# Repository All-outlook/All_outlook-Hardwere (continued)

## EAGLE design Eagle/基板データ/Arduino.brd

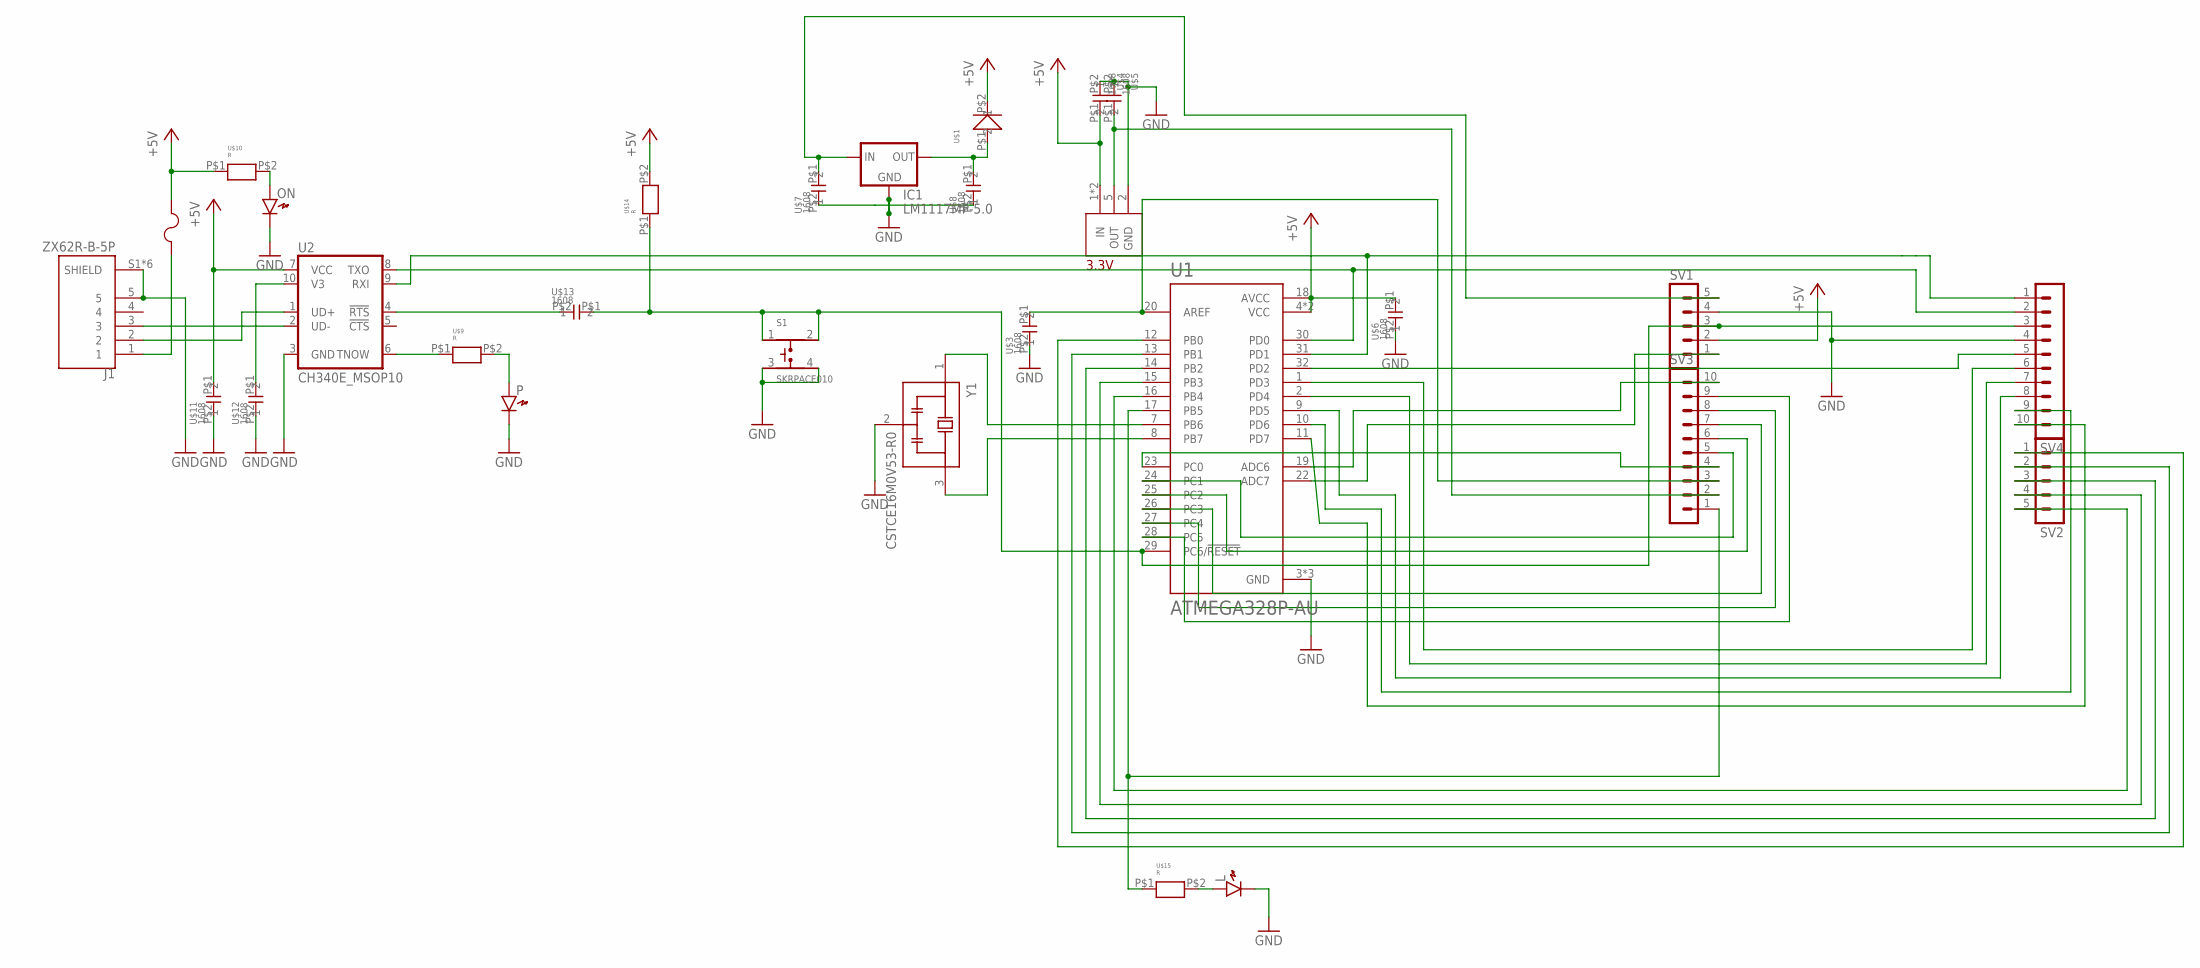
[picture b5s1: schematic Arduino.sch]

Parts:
IC1: LM1117MP-5.0; SOT223
J1: ZX62R-B-5P; HRS_ZX62R-B-5P
L: LED1608
ON: LED1608
P: LED1608
S1: SKRPACE010; SW_SKRPACE010
SV1, SV2: MA05-1
SV3, SV4: MA10-1
U1: ATMEGA328P-AU; QFP80P900X900X120-32N
U2: CH340E_MSOP10; MSOP10
U$1: D
U$2: 3.3V; SOT95P285X140-5N
U$3, U$4, U$5, U$6, U$7, U$8, U$11, U$12, U$13: 1608; CON
U$9, U$10, U$14, U$15: R; 1608
U$16: F
Y1: CSTCE16M0V53-R0; OSC_CSTCE16M0V53-R0

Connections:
+5V: SV1.2, U1.4 (VCC), U1.6 (VCC), U1.18 (AVCC), U2.7 (VCC), U$1.P$2 (2), U$2.1 (IN), U$2.3 (IN), U$4.P$1 (1), U$6.P$1 (1), U$10.P$1, U$11.P$1 (1), U$14.P$2, U$16.P$2
AREF: SV3.3, U1.20 (AREF), U$3.P$1 (1)
GND: IC1.1 (GND), J1.5, J1.S1 (SHIELD), J1.S2 (SHIELD), J1.S3 (SHIELD), J1.S4 (SHIELD), J1.S5 (SHIELD), J1.S6 (SHIELD), L.K, ON.K, P.K, S1.3, S1.4, SV1.4, SV4.4, U1.3 (GND), U1.5 (GND), U1.21 (GND), U2.3 (GND), U$2.2 (GND), U$3.P$2 (2), U$4.P$2 (2), U$5.P$2 (2), U$6.P$2 (2), U$7.P$2 (2), U$8.P$2 (2), U$11.P$2 (2), U$12.P$2 (2), Y1.2 (GND)
unnamed: U1.7 (PB6), Y1.1 (IN)
unnamed: U1.8 (PB7), Y1.3 (OUT)
unnamed: SV4.1, U1.31 (PD1), U2.9 (RXI)
unnamed: SV3.4, U1.23 (PC0)
unnamed: J1.1, U$16.P$1
unnamed: SV3.2, U$2.5 (OUT), U$5.P$1 (1)
unnamed: SV1.1, U1.22 (ADC7)
unnamed: IC1.2 (OUT), IC1.4 (OUT), U$1.P$1 (1), U$8.P$1 (1)
unnamed: IC1.3 (IN), SV1.5, U$7.P$1 (1)
unnamed: SV3.5, U1.24 (PC1)
unnamed: ON.A, U$10.P$2
unnamed: J1.2, U2.1 (UD+)
unnamed: J1.3, U2.2 (UD-)
unnamed: SV4.2, U1.30 (PD0), U2.8 (TXO)
unnamed: U2.10 (V3), U$12.P$1 (1)
unnamed: U2.6 (TNOW), U$9.P$1
unnamed: P.A, U$9.P$2
unnamed: U2.4 (!RTS), U$13.P$2 (2)
unnamed: S1.1, S1.2, SV1.3, SV4.3, U1.29 (PC6/!RESET), U$13.P$1 (1), U$14.P$1
unnamed: SV3.10, U1.19 (ADC6)
unnamed: SV3.6, U1.25 (PC2)
unnamed: SV3.7, U1.26 (PC3)
unnamed: SV3.8, U1.27 (PC4)
unnamed: SV3.9, U1.28 (PC5)
unnamed: SV3.1, U1.17 (PB5), U$15.P$1
unnamed: SV2.5, U1.16 (PB4)
unnamed: SV2.4, U1.15 (PB3)
unnamed: SV2.3, U1.14 (PB2)
unnamed: SV2.2, U1.13 (PB1)
unnamed: SV2.1, U1.12 (PB0)
unnamed: SV4.8, U1.9 (PD5)
unnamed: SV4.5, U1.32 (PD2)
unnamed: SV4.6, U1.1 (PD3)
unnamed: SV4.7, U1.2 (PD4)
unnamed: SV4.9, U1.10 (PD6)
unnamed: SV4.10, U1.11 (PD7)
unnamed: L.A, U$15.P$2

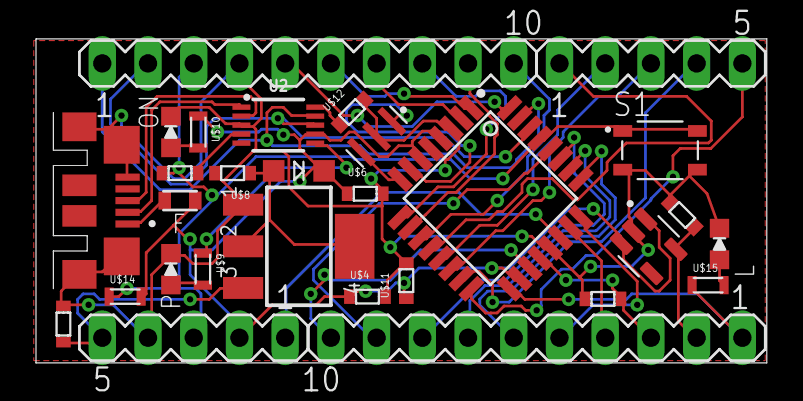
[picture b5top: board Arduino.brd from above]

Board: 2 copper layers, 40.6 x 18.0 mm, 29 parts (0 on the bottom side), 40 nets.

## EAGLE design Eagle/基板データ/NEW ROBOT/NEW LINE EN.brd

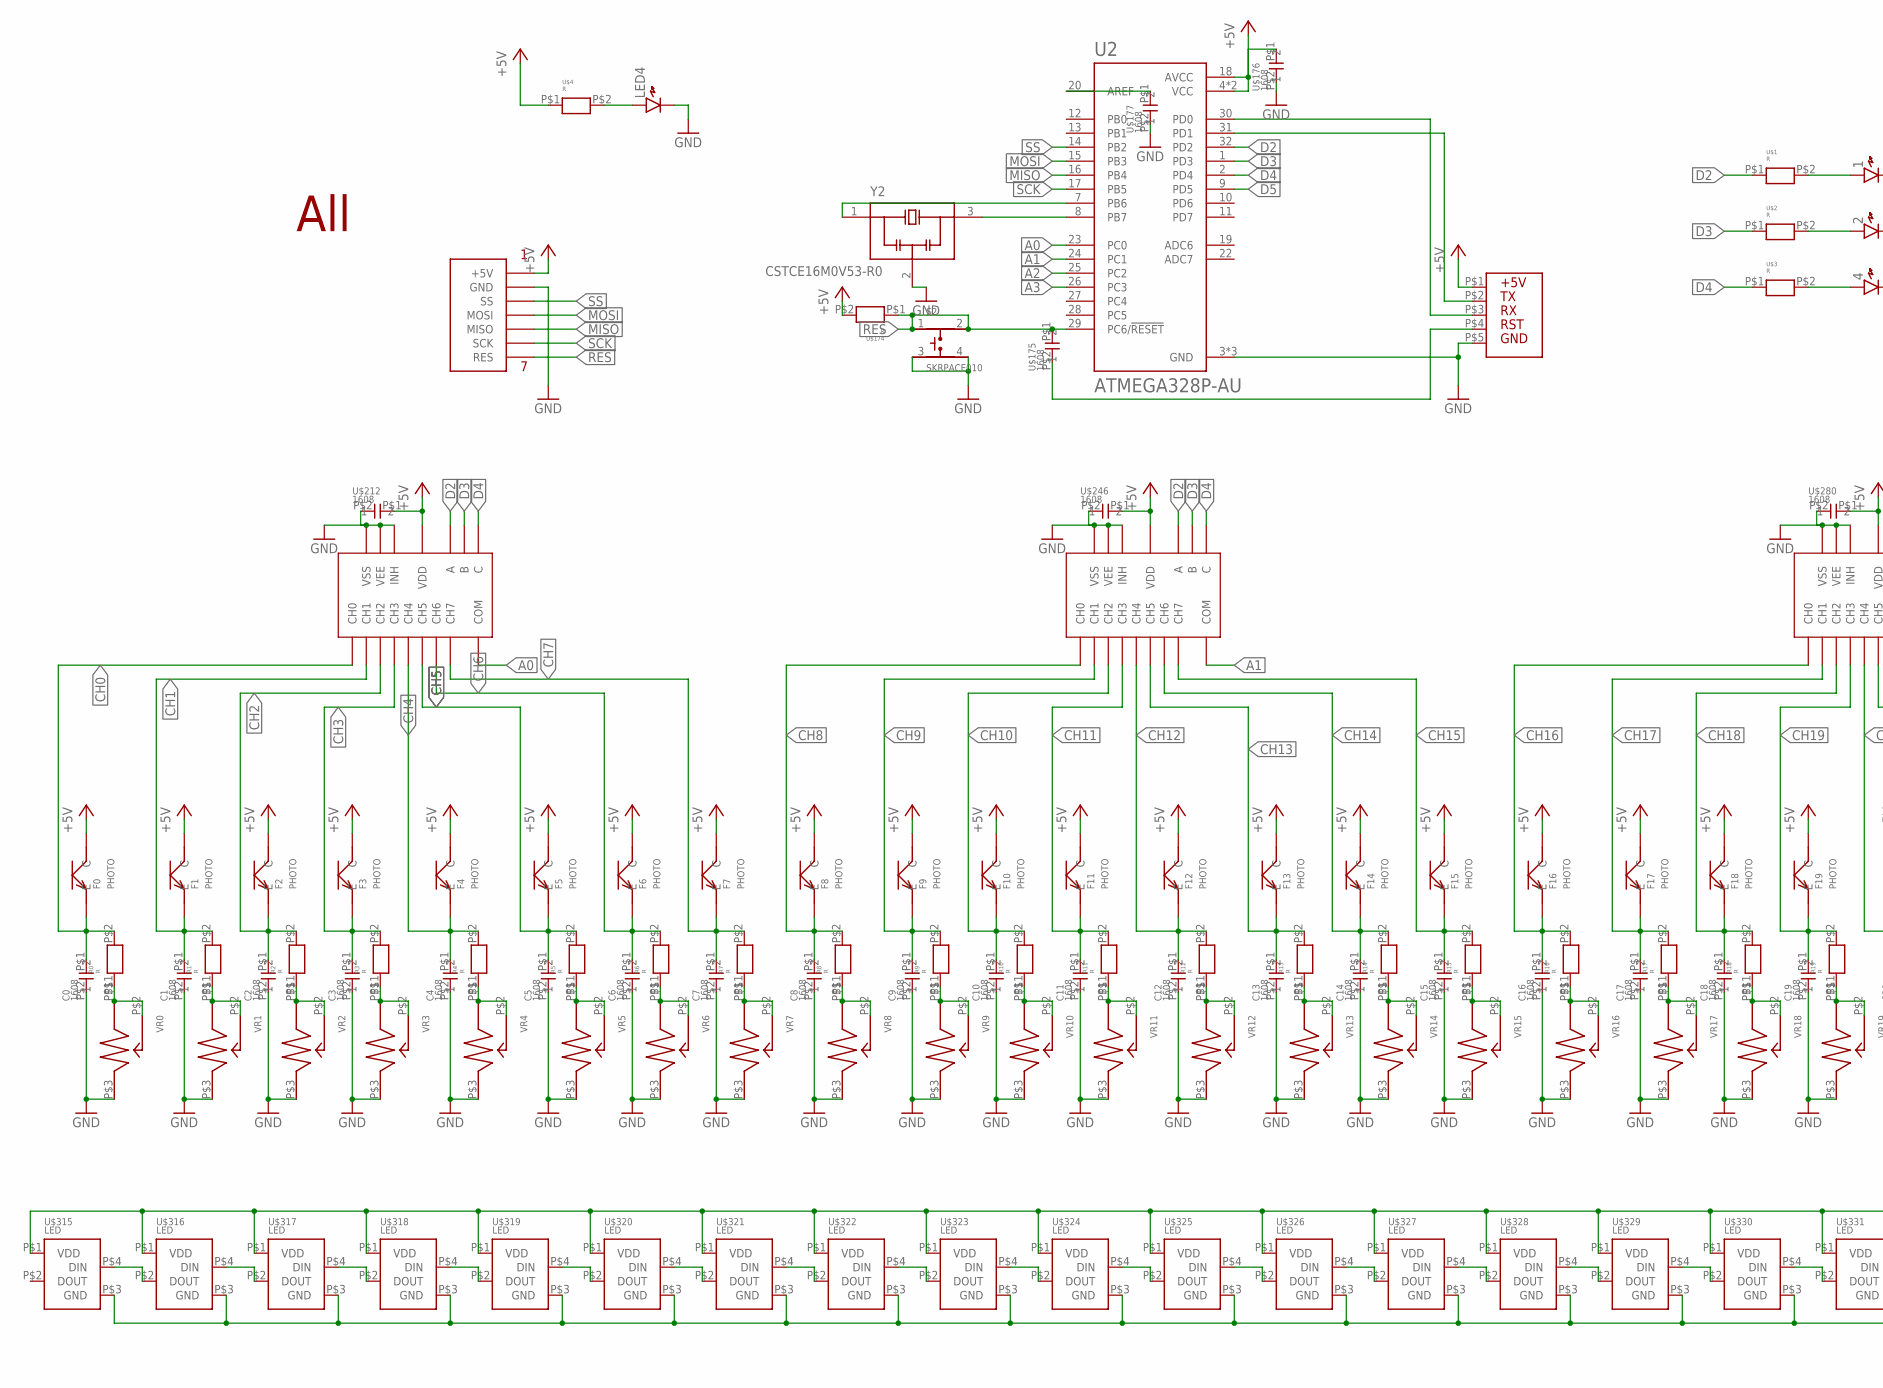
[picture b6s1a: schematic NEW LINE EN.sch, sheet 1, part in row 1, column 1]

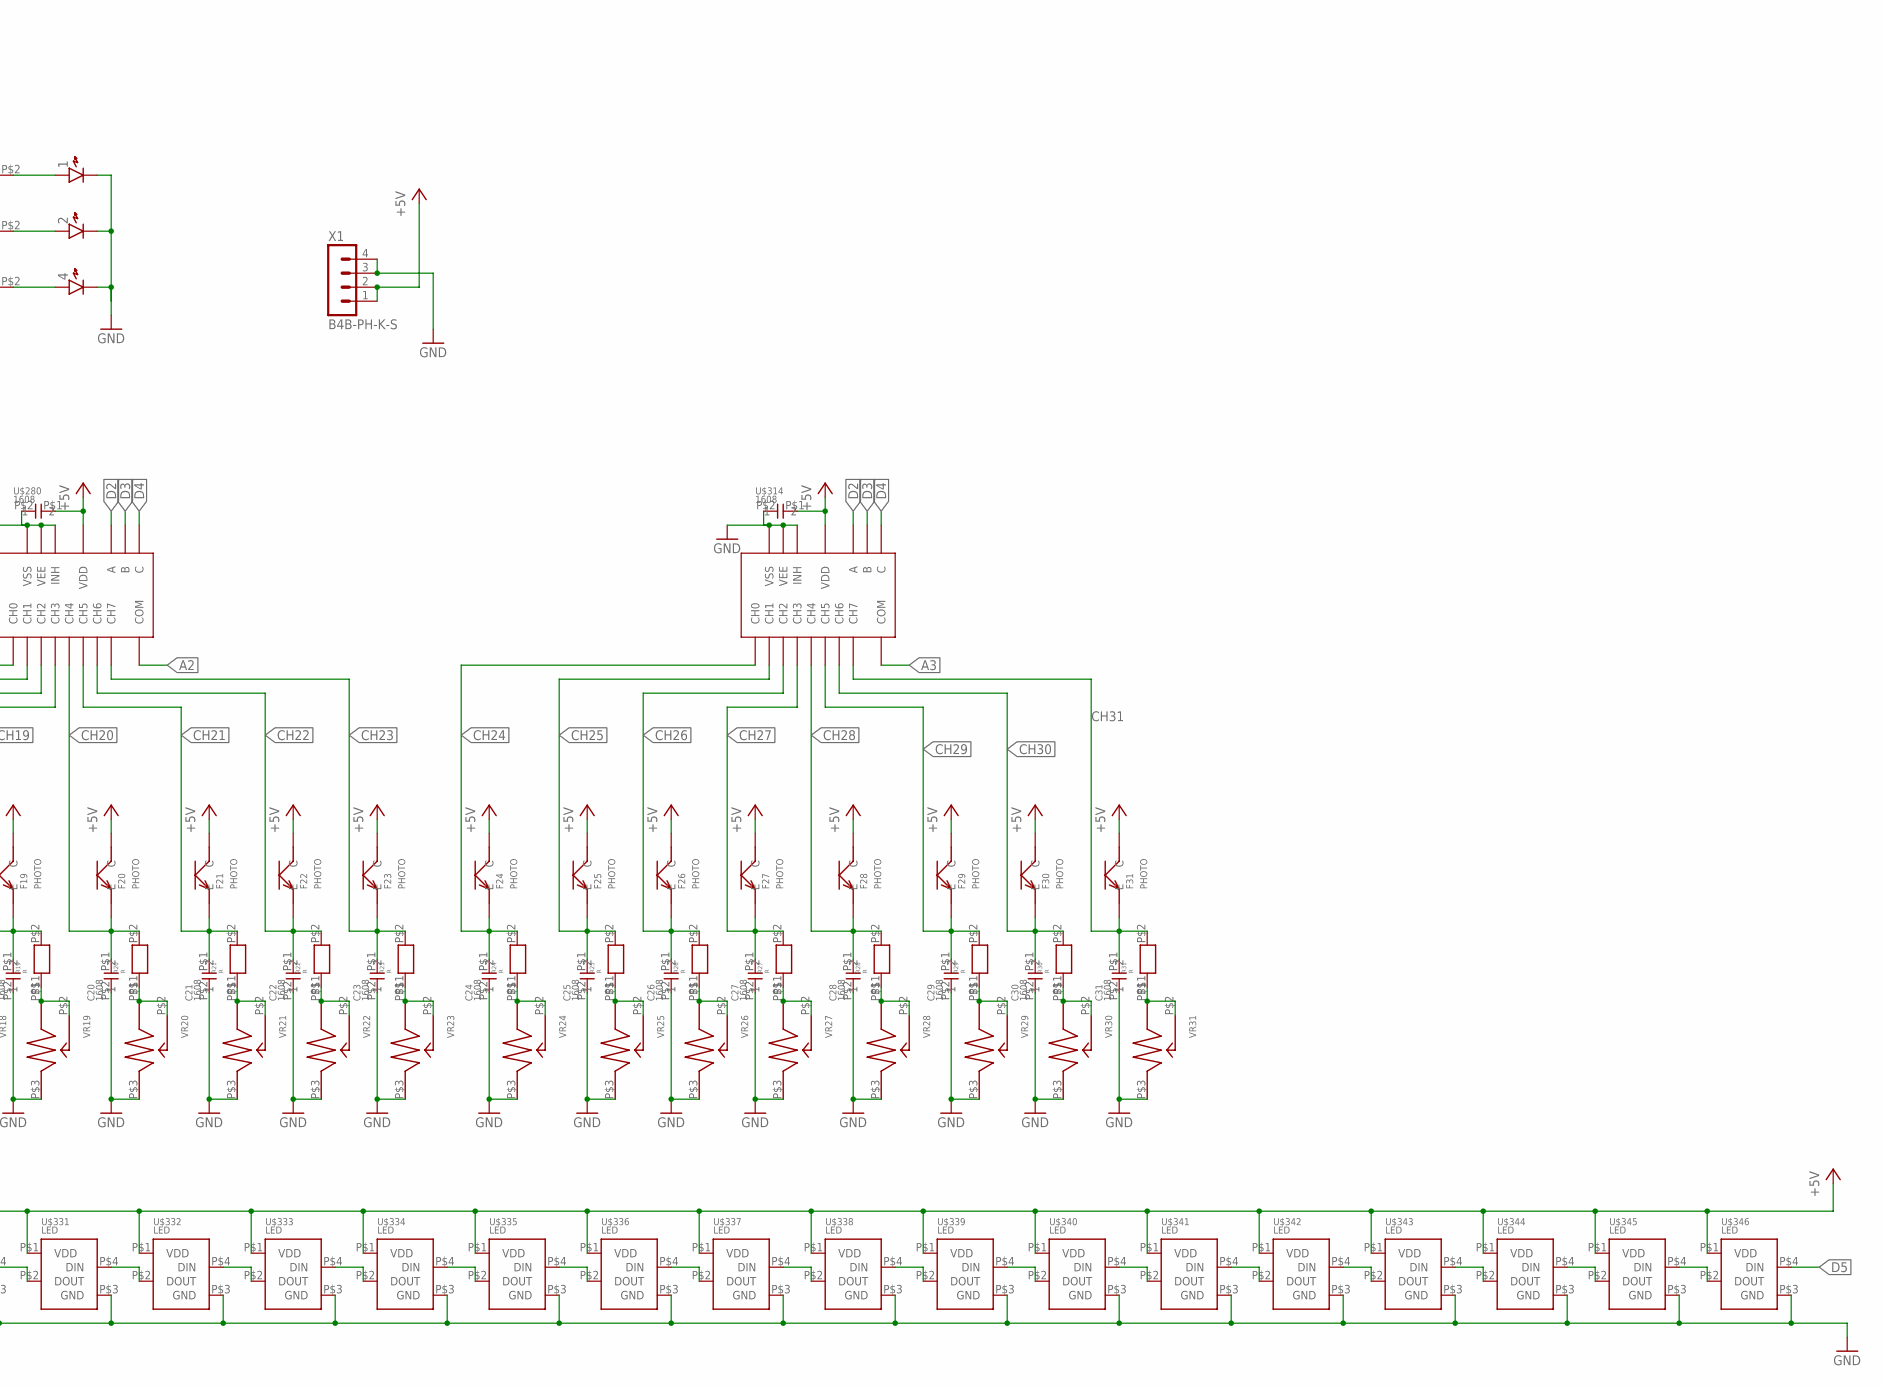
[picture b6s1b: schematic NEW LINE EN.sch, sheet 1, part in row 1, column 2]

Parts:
1, 2, 4: LED1608
C0, C1, C2, C3, C4, C5, C6, C7, C8, C9, C10, C11, C12, C13, C14, C15, C16, C17, C18, C19, C20, C21, C22, C23, C24, C25, C26, C27, C28, C29, C30, C31: 1608; CON
F0, F1, F2, F3, F4, F5, F6, F7, F8, F9, F10, F11, F12, F13, F14, F15, F16, F17, F18, F19, F20, F21, F22, F23, F24, F25, F26, F27, F28, F29, F30, F31: PHOTO
LED4: LED1608
R0, R1, R2, R3, R4, R5, R6, R7, R8, R9, R10, R11, R12, R13, R14, R15, R16, R17, R18, R19, R20, R21, R22, R23, R24, R25, R26, R27, R28, R29, R30, R31: R; 1608
S2: SKRPACE010; SW_SKRPACE010
U2: ATMEGA328P-AU; QFP80P900X900X120-32N
U$1, U$2, U$3, U$4, U$174: R; 1608
U$5: SPI
U$6: SI
U$7: ALL
U$175, U$176, U$177, U$212, U$246, U$280, U$314: 1608; CON
U$179, U$213, U$247, U$281: AM; SOP65P640X120-16N
U$315, U$316, U$317, U$318, U$319, U$320, U$321, U$322, U$323, U$324, U$325, U$326, U$327, U$328, U$329, U$330, U$331, U$332, U$333, U$334, U$335, U$336, U$337, U$338, U$339, U$340, U$341, U$342, U$343, U$344, U$345, U$346: LED
VR0, VR1, VR2, VR3, VR4, VR5, VR6, VR7, VR8, VR9, VR10, VR11, VR12, VR13, VR14, VR15, VR16, VR17, VR18, VR19, VR20, VR21, VR22, VR23, VR24, VR25, VR26, VR27, VR28, VR29, VR30, VR31: VR
X1: B4B-PH-K-S
Y2: CSTCE16M0V53-R0; OSC_CSTCE16M0V53-R0

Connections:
+5V: F0.P$1 (C), F1.P$1 (C), F2.P$1 (C), F3.P$1 (C), F4.P$1 (C), F5.P$1 (C), F6.P$1 (C), F7.P$1 (C), F8.P$1 (C), F9.P$1 (C), F10.P$1 (C), F11.P$1 (C), F12.P$1 (C), F13.P$1 (C), F14.P$1 (C), F15.P$1 (C), F16.P$1 (C), F17.P$1 (C), F18.P$1 (C), F19.P$1 (C), F20.P$1 (C), F21.P$1 (C), F22.P$1 (C), F23.P$1 (C), F24.P$1 (C), F25.P$1 (C), F26.P$1 (C), F27.P$1 (C), F28.P$1 (C), F29.P$1 (C), F30.P$1 (C), F31.P$1 (C), U2.4 (VCC), U2.6 (VCC), U2.18 (AVCC), U$4.P$1, U$5.P$1 (+5V), U$6.P$1, U$174.P$2, U$176.P$1 (1), U$179.16 (VDD), U$212.P$1 (1), U$213.16 (VDD), U$246.P$1 (1), U$247.16 (VDD), U$280.P$1 (1), U$281.16 (VDD), U$314.P$1 (1), U$315.P$1 (VDD), U$316.P$1 (VDD), U$317.P$1 (VDD), U$318.P$1 (VDD), U$319.P$1 (VDD), U$320.P$1 (VDD), U$321.P$1 (VDD), U$322.P$1 (VDD), U$323.P$1 (VDD), U$324.P$1 (VDD), U$325.P$1 (VDD), U$326.P$1 (VDD), U$327.P$1 (VDD), U$328.P$1 (VDD), U$329.P$1 (VDD), U$330.P$1 (VDD), U$331.P$1 (VDD), U$332.P$1 (VDD), U$333.P$1 (VDD), U$334.P$1 (VDD), U$335.P$1 (VDD), U$336.P$1 (VDD), U$337.P$1 (VDD), U$338.P$1 (VDD), U$339.P$1 (VDD), U$340.P$1 (VDD), U$341.P$1 (VDD), U$342.P$1 (VDD), U$343.P$1 (VDD), U$344.P$1 (VDD), U$345.P$1 (VDD), U$346.P$1 (VDD), X1.1, X1.2
A0: U2.23 (PC0), U$179.3 (COM)
A1: U2.24 (PC1), U$213.3 (COM)
A2: U2.25 (PC2), U$247.3 (COM)
A3: U2.26 (PC3), U$281.3 (COM)
CH0: C0.P$1 (1), F0.P$2 (E), R0.P$2, U$179.13 (CH0)
CH1: C1.P$1 (1), F1.P$2 (E), R1.P$2, U$179.14 (CH1)
CH2: C2.P$1 (1), F2.P$2 (E), R2.P$2, U$179.15 (CH2)
CH3: C3.P$1 (1), F3.P$2 (E), R3.P$2, U$179.12 (CH3)
CH4: C4.P$1 (1), F4.P$2 (E), R4.P$2, U$179.1 (CH4)
CH5: C5.P$1 (1), F5.P$2 (E), R5.P$2, U$179.5 (CH5)
CH6: C6.P$1 (1), F6.P$2 (E), R6.P$2, U$179.2 (CH6)
CH7: C7.P$1 (1), F7.P$2 (E), R7.P$2, U$179.4 (CH7)
CH8: C8.P$1 (1), F8.P$2 (E), R8.P$2, U$213.13 (CH0)
CH9: C9.P$1 (1), F9.P$2 (E), R9.P$2, U$213.14 (CH1)
CH10: C10.P$1 (1), F10.P$2 (E), R10.P$2, U$213.15 (CH2)
CH11: C11.P$1 (1), F11.P$2 (E), R11.P$2, U$213.12 (CH3)
CH12: C12.P$1 (1), F12.P$2 (E), R12.P$2, U$213.1 (CH4)
CH13: C13.P$1 (1), F13.P$2 (E), R13.P$2, U$213.5 (CH5)
CH14: C14.P$1 (1), F14.P$2 (E), R14.P$2, U$213.2 (CH6)
CH15: C15.P$1 (1), F15.P$2 (E), R15.P$2, U$213.4 (CH7)
CH16: C16.P$1 (1), F16.P$2 (E), R16.P$2, U$247.13 (CH0)
CH17: C17.P$1 (1), F17.P$2 (E), R17.P$2, U$247.14 (CH1)
CH18: C18.P$1 (1), F18.P$2 (E), R18.P$2, U$247.15 (CH2)
CH19: C19.P$1 (1), F19.P$2 (E), R19.P$2, U$247.12 (CH3)
CH20: C20.P$1 (1), F20.P$2 (E), R20.P$2, U$247.1 (CH4)
CH21: C21.P$1 (1), F21.P$2 (E), R21.P$2, U$247.5 (CH5)
CH22: C22.P$1 (1), F22.P$2 (E), R22.P$2, U$247.2 (CH6)
CH23: C23.P$1 (1), F23.P$2 (E), R23.P$2, U$247.4 (CH7)
CH24: C24.P$1 (1), F24.P$2 (E), R24.P$2, U$281.13 (CH0)
CH25: C25.P$1 (1), F25.P$2 (E), R25.P$2, U$281.14 (CH1)
CH26: C26.P$1 (1), F26.P$2 (E), R26.P$2, U$281.15 (CH2)
CH27: C27.P$1 (1), F27.P$2 (E), R27.P$2, U$281.12 (CH3)
CH28: C28.P$1 (1), F28.P$2 (E), R28.P$2, U$281.1 (CH4)
CH29: C29.P$1 (1), F29.P$2 (E), R29.P$2, U$281.5 (CH5)
CH30: C30.P$1 (1), F30.P$2 (E), R30.P$2, U$281.2 (CH6)
CH31: C31.P$1 (1), F31.P$2 (E), R31.P$2, U$281.4 (CH7)
D2: U2.32 (PD2), U$1.P$1, U$179.11 (A), U$213.11 (A), U$247.11 (A), U$281.11 (A)
D3: U2.1 (PD3), U$2.P$1, U$179.10 (B), U$213.10 (B), U$247.10 (B), U$281.10 (B)
D4: U2.2 (PD4), U$3.P$1, U$179.9 (C), U$213.9 (C), U$247.9 (C), U$281.9 (C)
D5: U2.9 (PD5), U$346.P$4 (DIN)
GND: 1.K, 2.K, 4.K, C0.P$2 (2), C1.P$2 (2), C2.P$2 (2), C3.P$2 (2), C4.P$2 (2), C5.P$2 (2), C6.P$2 (2), C7.P$2 (2), C8.P$2 (2), C9.P$2 (2), C10.P$2 (2), C11.P$2 (2), C12.P$2 (2), C13.P$2 (2), C14.P$2 (2), C15.P$2 (2), C16.P$2 (2), C17.P$2 (2), C18.P$2 (2), C19.P$2 (2), C20.P$2 (2), C21.P$2 (2), C22.P$2 (2), C23.P$2 (2), C24.P$2 (2), C25.P$2 (2), C26.P$2 (2), C27.P$2 (2), C28.P$2 (2), C29.P$2 (2), C30.P$2 (2), C31.P$2 (2), LED4.K, S2.3, S2.4, U2.3 (GND), U2.5 (GND), U2.21 (GND), U$5.P$2 (GND), U$6.P$5, U$176.P$2 (2), U$177.P$2 (2), U$179.6 (INH), U$179.7 (VEE), U$179.8 (VSS), U$212.P$2 (2), U$213.6 (INH), U$213.7 (VEE), U$213.8 (VSS), U$246.P$2 (2), U$247.6 (INH), U$247.7 (VEE), U$247.8 (VSS), U$280.P$2 (2), U$281.6 (INH), U$281.7 (VEE), U$281.8 (VSS), U$314.P$2 (2), U$315.P$3 (GND), U$316.P$3 (GND), U$317.P$3 (GND), U$318.P$3 (GND), U$319.P$3 (GND), U$320.P$3 (GND), U$321.P$3 (GND), U$322.P$3 (GND), U$323.P$3 (GND), U$324.P$3 (GND), U$325.P$3 (GND), U$326.P$3 (GND), U$327.P$3 (GND), U$328.P$3 (GND), U$329.P$3 (GND), U$330.P$3 (GND), U$331.P$3 (GND), U$332.P$3 (GND), U$333.P$3 (GND), U$334.P$3 (GND), U$335.P$3 (GND), U$336.P$3 (GND), U$337.P$3 (GND), U$338.P$3 (GND), U$339.P$3 (GND), U$340.P$3 (GND), U$341.P$3 (GND), U$342.P$3 (GND), U$343.P$3 (GND), U$344.P$3 (GND), U$345.P$3 (GND), U$346.P$3 (GND), VR0.P$3, VR1.P$3, VR2.P$3, VR3.P$3, VR4.P$3, VR5.P$3, VR6.P$3, VR7.P$3, VR8.P$3, VR9.P$3, VR10.P$3, VR11.P$3, VR12.P$3, VR13.P$3, VR14.P$3, VR15.P$3, VR16.P$3, VR17.P$3, VR18.P$3, VR19.P$3, VR20.P$3, VR21.P$3, VR22.P$3, VR23.P$3, VR24.P$3, VR25.P$3, VR26.P$3, VR27.P$3, VR28.P$3, VR29.P$3, VR30.P$3, VR31.P$3, X1.3, X1.4, Y2.2 (GND)
MISO: U2.16 (PB4), U$5.P$5 (MISO)
MOSI: U2.15 (PB3), U$5.P$4 (MOSI)
unnamed: 4.A, U$3.P$2
unnamed: 2.A, U$2.P$2
unnamed: 1.A, U$1.P$2
unnamed: LED4.A, U$4.P$2
unnamed: U2.20 (AREF), U$177.P$1 (1)
unnamed: U$6.P$4, U$175.P$2 (2)
unnamed: U2.31 (PD1), U$6.P$2
unnamed: U2.30 (PD0), U$6.P$3
unnamed: U2.7 (PB6), Y2.1 (IN)
unnamed: U2.8 (PB7), Y2.3 (OUT)
unnamed: R0.P$1, VR0.P$1, VR0.P$2
unnamed: R1.P$1, VR1.P$1, VR1.P$2
unnamed: R2.P$1, VR2.P$1, VR2.P$2
unnamed: R3.P$1, VR3.P$1, VR3.P$2
unnamed: R4.P$1, VR4.P$1, VR4.P$2
unnamed: R5.P$1, VR5.P$1, VR5.P$2
unnamed: R6.P$1, VR6.P$1, VR6.P$2
unnamed: R7.P$1, VR7.P$1, VR7.P$2
unnamed: R8.P$1, VR8.P$1, VR8.P$2
unnamed: R9.P$1, VR9.P$1, VR9.P$2
unnamed: R10.P$1, VR10.P$1, VR10.P$2
unnamed: R11.P$1, VR11.P$1, VR11.P$2
unnamed: R12.P$1, VR12.P$1, VR12.P$2
unnamed: R13.P$1, VR13.P$1, VR13.P$2
unnamed: R14.P$1, VR14.P$1, VR14.P$2
unnamed: R15.P$1, VR15.P$1, VR15.P$2
unnamed: R16.P$1, VR16.P$1, VR16.P$2
unnamed: R17.P$1, VR17.P$1, VR17.P$2
unnamed: R18.P$1, VR18.P$1, VR18.P$2
unnamed: R19.P$1, VR19.P$1, VR19.P$2
unnamed: R20.P$1, VR20.P$1, VR20.P$2
unnamed: R21.P$1, VR21.P$1, VR21.P$2
unnamed: R22.P$1, VR22.P$1, VR22.P$2
unnamed: R23.P$1, VR23.P$1, VR23.P$2
unnamed: R24.P$1, VR24.P$1, VR24.P$2
unnamed: R25.P$1, VR25.P$1, VR25.P$2
unnamed: R26.P$1, VR26.P$1, VR26.P$2
unnamed: R27.P$1, VR27.P$1, VR27.P$2
unnamed: R28.P$1, VR28.P$1, VR28.P$2
unnamed: R29.P$1, VR29.P$1, VR29.P$2
unnamed: R30.P$1, VR30.P$1, VR30.P$2
unnamed: R31.P$1, VR31.P$1, VR31.P$2
unnamed: U$315.P$4 (DIN), U$316.P$2 (DOUT)
unnamed: U$316.P$4 (DIN), U$317.P$2 (DOUT)
unnamed: U$319.P$4 (DIN), U$320.P$2 (DOUT)
unnamed: U$320.P$4 (DIN), U$321.P$2 (DOUT)
unnamed: U$321.P$4 (DIN), U$322.P$2 (DOUT)
unnamed: U$317.P$4 (DIN), U$318.P$2 (DOUT)
unnamed: U$318.P$4 (DIN), U$319.P$2 (DOUT)
unnamed: U$323.P$4 (DIN), U$324.P$2 (DOUT)
unnamed: U$324.P$4 (DIN), U$325.P$2 (DOUT)
unnamed: U$327.P$4 (DIN), U$328.P$2 (DOUT)
unnamed: U$328.P$4 (DIN), U$329.P$2 (DOUT)
unnamed: U$329.P$4 (DIN), U$330.P$2 (DOUT)
unnamed: U$325.P$4 (DIN), U$326.P$2 (DOUT)
unnamed: U$326.P$4 (DIN), U$327.P$2 (DOUT)
unnamed: U$331.P$4 (DIN), U$332.P$2 (DOUT)
unnamed: U$332.P$4 (DIN), U$333.P$2 (DOUT)
unnamed: U$335.P$4 (DIN), U$336.P$2 (DOUT)
unnamed: U$336.P$4 (DIN), U$337.P$2 (DOUT)
unnamed: U$337.P$4 (DIN), U$338.P$2 (DOUT)
unnamed: U$333.P$4 (DIN), U$334.P$2 (DOUT)
unnamed: U$334.P$4 (DIN), U$335.P$2 (DOUT)
unnamed: U$339.P$4 (DIN), U$340.P$2 (DOUT)
unnamed: U$340.P$4 (DIN), U$341.P$2 (DOUT)
unnamed: U$343.P$4 (DIN), U$344.P$2 (DOUT)
unnamed: U$344.P$4 (DIN), U$345.P$2 (DOUT)
unnamed: U$345.P$4 (DIN), U$346.P$2 (DOUT)
unnamed: U$341.P$4 (DIN), U$342.P$2 (DOUT)
unnamed: U$342.P$4 (DIN), U$343.P$2 (DOUT)
unnamed: U$322.P$4 (DIN), U$323.P$2 (DOUT)
unnamed: U$330.P$4 (DIN), U$331.P$2 (DOUT)
unnamed: U$338.P$4 (DIN), U$339.P$2 (DOUT)
RES: S2.1, S2.2, U2.29 (PC6/!RESET), U$5.P$7 (RES), U$174.P$1, U$175.P$1 (1)
SCK: U2.17 (PB5), U$5.P$6 (SCK)
SS: U2.14 (PB2), U$5.P$3 (SS)

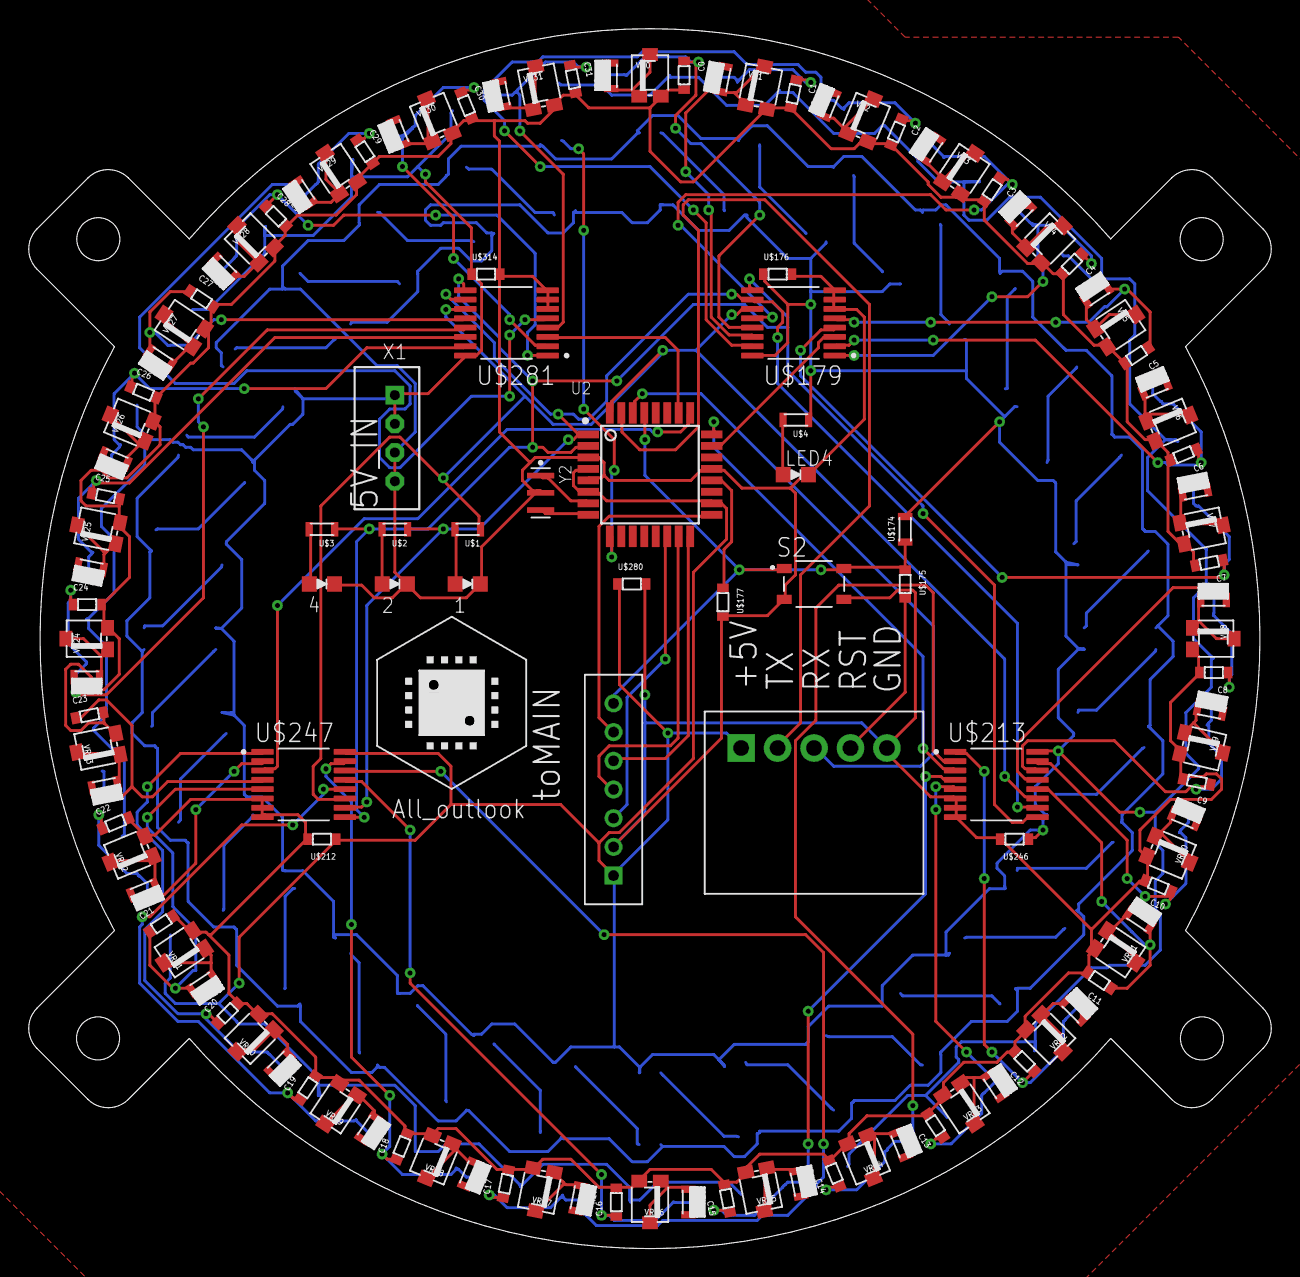
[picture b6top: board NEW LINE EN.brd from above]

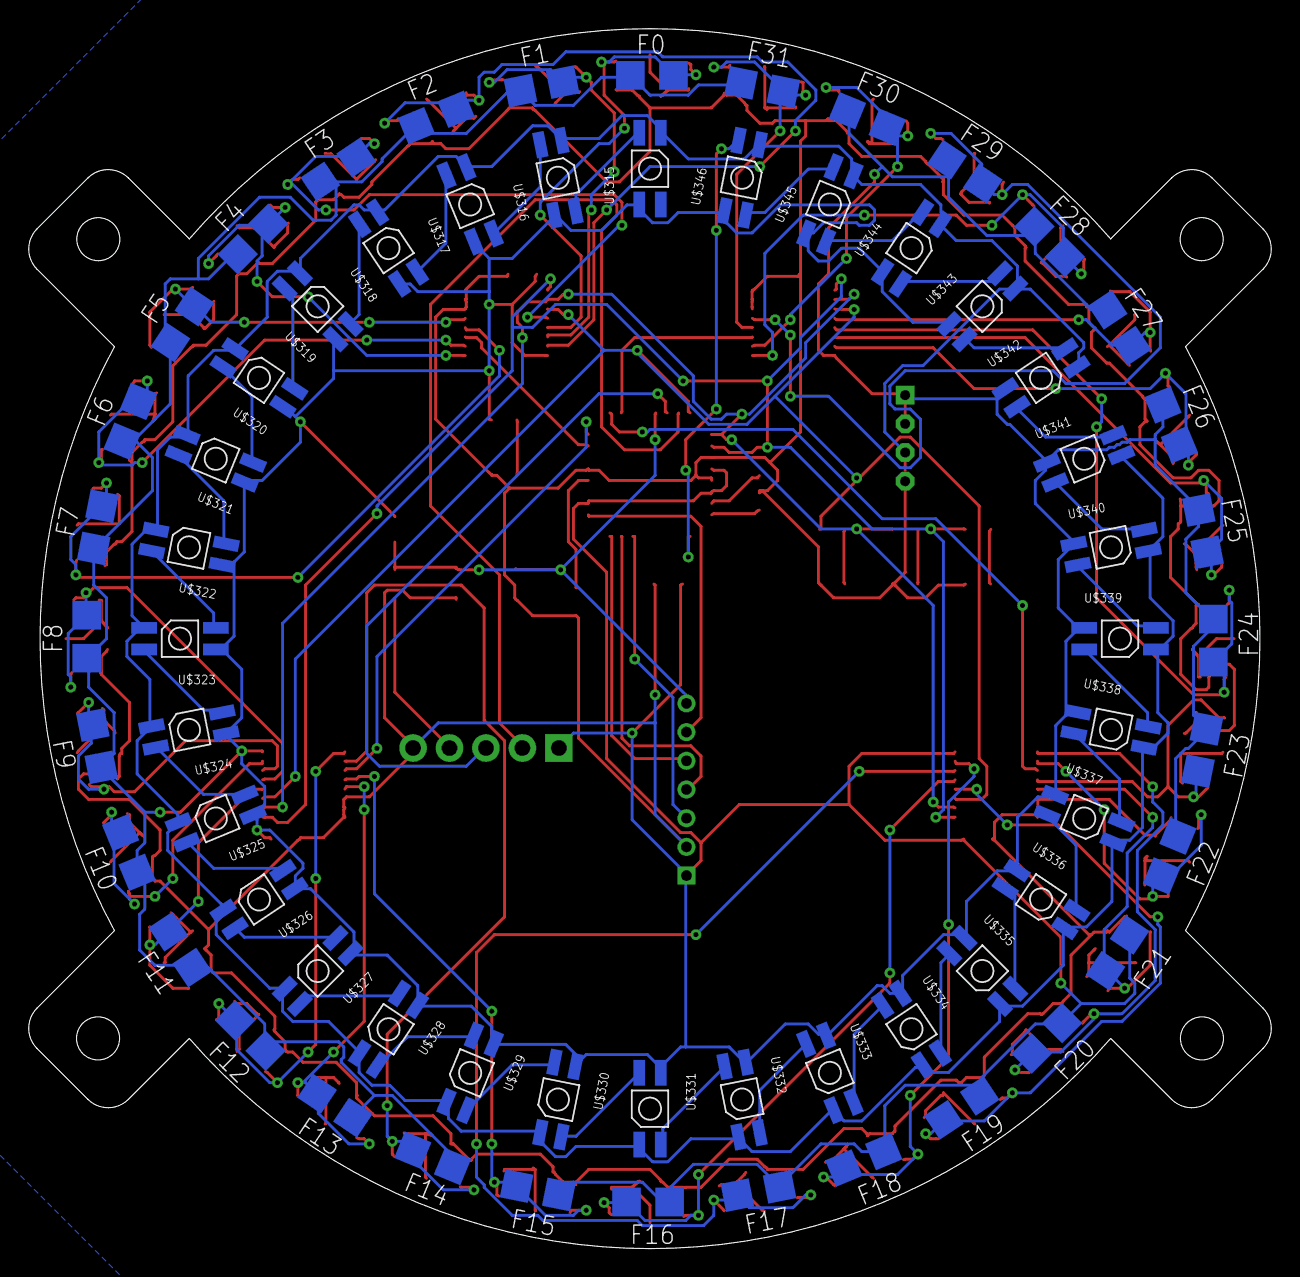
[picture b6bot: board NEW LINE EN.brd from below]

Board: 2 copper layers, 86.6 x 85.0 mm, 187 parts (32 on the bottom side), 120 nets.
